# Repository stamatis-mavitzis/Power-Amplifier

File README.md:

<div align="center">

# Hi‑Fi Class‑AB Power Amplifier

### Stereo discrete power amplifier with dual 500 VA supplies, STM32 speaker protection, thermal monitoring, KiCad hardware, firmware, and measured prototype validation

**KiCad · Discrete Class‑AB · ≈±34.5 V Idle Rails · STM32G031K8 · Speaker Protection · Thermal Monitoring**

</div>

---

## Overview

This repository contains the design, implementation, firmware, fabrication files, and measured validation of a two-channel discrete **Hi‑Fi Class‑AB power amplifier** developed in **KiCad**.

The power-amplifier stage is based on the design principles of **Rod Elliott's Elliott Sound Products (ESP) Project 3A**. This implementation expands that reference design into a complete stereo amplifier system with:

- one dedicated **500 VA transformer per audio channel**;
- independent high-current rectification and filtering for the left and right channels;
- custom amplifier and power-supply PCBs;
- **MJL21193G / MJL21194G** complementary output devices;
- a dedicated **STM32G031K8 speaker-protection controller**;
- independent left/right DC monitoring;
- dual heatsink-temperature monitoring;
- relay-controlled speaker outputs;
- firmware for startup delay, fault handling, thermal protection, and status indication;
- measured electrical validation of the completed prototype.

The repository is intended to document the project from schematic design and PCB layout through assembly, firmware, bring-up, and bench testing.

---

## Project Status

The amplifier has progressed beyond the design-only stage.

Current status:

- amplifier PCBs assembled;
- power-supply hardware assembled;
- dual-transformer stereo supply implemented;
- STM32 protection system programmed and tested;
- left and right amplifier channels operational;
- speaker relays and protection functions tested;
- DC operating points measured;
- quiescent bias measured cold and warm;
- rail voltages measured at idle and under 8 Ω load;
- rail ripple measured under load;
- frequency-response checks completed;
- upper −3 dB point measured;
- final bench-test results recorded.

The project should therefore be described as a **built and functionally validated prototype**, not only as a planned or fabrication-ready design.

---

## Table of Contents

- [Key Features](#key-features)
- [Technical Summary](#technical-summary)
- [Measured Performance](#measured-performance)
- [System Architecture](#system-architecture)
- [Power Amplifier](#power-amplifier)
- [Power Supply](#power-supply)
- [STM32 Protection Controller](#stm32-protection-controller)
- [Protection Logic](#protection-logic)
- [Thermal Management](#thermal-management)
- [PCB Design Strategy](#pcb-design-strategy)
- [Grounding Strategy](#grounding-strategy)
- [Major Components](#major-components)
- [Test Equipment](#test-equipment)
- [Repository Structure](#repository-structure)
- [Manufacturing Files](#manufacturing-files)
- [Bring-Up and Validation](#bring-up-and-validation)
- [Measurement Limitations](#measurement-limitations)
- [Safety](#safety)
- [Design Tools](#design-tools)
- [Reference Design and Credits](#reference-design-and-credits)
- [Author](#author)

---

## Key Features

### Audio Power Stage

- Two-channel discrete **Class‑AB** architecture
- One amplifier PCB per channel
- Complementary bipolar output stage
- **MJL21193G / MJL21194G** complementary output transistor pair
- **BD139 / BD140** driver stage
- **0.33 Ω / 5 W** emitter resistors
- Through-hole power devices for serviceability and heatsink mounting
- Dedicated external heatsink for each amplifier channel
- On-board **3 A** positive- and negative-rail fuses

### Main Power Supply

- **2 × 500 VA transformers**
- One transformer dedicated to the **left channel**
- One transformer dedicated to the **right channel**
- Nominal dual low-voltage secondary windings
- Measured transformer secondary voltages of approximately **25.5–25.7 VRMS per half-secondary**
- High-current bridge rectification
- **KBPC3506WP** bridge rectifier in the power-supply design
- Four **4700 µF** reservoir capacitors on the power-supply schematic
- Measured idle rails of approximately **+34.5 V / −34.5 V**
- Measured loaded rails of approximately **±33.5 to ±33.7 V** with an 8 Ω load

### Protection and Monitoring

- **ST NUCLEO‑G031K8**
- **STM32G031K8** microcontroller
- Independent left/right amplifier-output monitoring
- Independent left/right heatsink-temperature monitoring
- 10 kΩ NTC thermistors
- Startup speaker delay
- Persistent-DC fault detection
- Overtemperature shutdown
- Sensor-fault handling
- Latched fault handling and reset
- Relay-controlled left/right speaker outputs
- Front-panel status indication

### Mechanical and Thermal Design

- Large external heatsinks
- Passive natural-convection cooling
- Power transistors positioned near PCB edges for heatsink mounting
- Electrical insulation between power-transistor tabs and heatsink where required
- Metal-chassis integration
- Star-ground implementation
- Chassis protective-earth bonding
- High-current speaker and supply wiring separated from low-level input wiring

---

## Technical Summary

| Parameter | Final implementation |
|---|---|
| Amplifier topology | Discrete Class‑AB |
| Number of channels | 2 |
| Main transformers | **2 × 500 VA**, one per channel |
| Measured secondary voltage | ≈25.5–25.7 VRMS from each outer secondary lead to center tap |
| Measured idle rails | ≈+34.5 V / −34.5 V |
| Measured rails under 8 Ω test load | ≈±33.5 to ±33.7 V |
| Output devices | **MJL21194G (NPN) / MJL21193G (PNP)** |
| Output-device package | **TO‑264, through-hole** |
| Driver devices | **BD139 / BD140** |
| Output emitter resistors | **R13 / R14 = 0.33 Ω, 5 W** |
| Amplifier rail fuses | **3 A** |
| Protection controller | ST NUCLEO‑G031K8 |
| MCU | STM32G031K8 |
| Speaker relays | 2 × Omron G2RL‑1A‑E‑DC12 |
| Relay driver | BC337 NPN |
| Temperature sensing | 2 × 10 kΩ NTC |
| Cooling | External heatsinks, passive natural convection |
| Audio inputs | RCA |
| Speaker outputs | Chassis-mounted binding terminals |
| PCB CAD | KiCad |

---

# Measured Performance

The following values were measured on the completed prototype. They are reported as **bench-test results**, not as guaranteed production specifications.

## Transformer Secondary Voltages

Measured from each AC secondary lead to the center tap:

| Measurement | Left | Right |
|---|---:|---:|
| AC1 → center tap | 25.652 VRMS | 25.628 VRMS |
| AC2 → center tap | 25.631 VRMS | 25.516 VRMS |

The measurements show good agreement between the two transformer channels.

## DC Supply Rails

### Idle

| Rail | Left | Right |
|---|---:|---:|
| Positive | +34.521 V | +34.566 V |
| Negative | −34.532 V | −34.522 V |

### Under 8 Ω Amplifier Load

| Rail | Left | Right |
|---|---:|---:|
| Positive | +33.534 V | +33.678 V |
| Negative | −33.560 V | −33.701 V |

The measured rail reduction under the recorded load condition is approximately 0.8–1.0 V compared with idle.

## Rail Ripple Under 8 Ω Load

Recorded ripple values:

| Rail | Left | Right |
|---|---:|---:|
| Positive rail | 1.5 V | 1.4 V |
| Negative rail | 1.6 V | 1.4 V |

These values are reproduced as recorded in the measurement log. They should not be interpreted as a different RMS or peak-to-peak quantity unless the oscilloscope measurement mode used during the test is also specified.

## Quiescent Bias

Bias was measured as the voltage across **R13 + R14**.

Because each emitter resistor is **0.33 Ω**, the combined resistance is **0.66 Ω**.

| Channel | Cold voltage | Approx. cold current | Warm voltage | Approx. warm current |
|---|---:|---:|---:|---:|
| Left | 41.700 mV | 63.2 mA | 52.55 mV | 79.6 mA |
| Right | 41.730 mV | 63.2 mA | 55.71 mV | 84.4 mA |

The increase from cold to warm operation is documented so that bias thermal behaviour remains traceable.

## DC Output Offset

Initial recorded DC-offset measurements:

| Channel | DC offset |
|---|---:|
| Left | −54.54 mV |
| Right | −28.203 mV |

A later no-signal measurement recorded:

| Channel | Amplifier output |
|---|---:|
| Left | +42.300 mV |
| Right | −23.764 mV |

Because these measurements were taken at different points in the test sequence, they are retained separately rather than combined into a single nominal value.

## Frequency Response and Voltage Gain

With:

- input signal: **1.2 V peak-to-peak**;
- sine-wave test;
- test frequencies: **20 Hz, 50 Hz, 100 Hz, 500 Hz, 1 kHz, 5 kHz, 10 kHz, 20 kHz**;

the recorded output was approximately:

- Left: **22.6 V peak-to-peak**
- Right: **22.6 V peak-to-peak**

This corresponds to:

- voltage gain: **18.83 V/V**
- voltage gain: **25.50 dB**

No significant amplitude reduction was recorded over the tested **20 Hz to 20 kHz** audio band.

The recorded **upper −3 dB frequency** is approximately:

**250 kHz**

The protection controller may interpret very-low-frequency content below approximately **15 Hz** as a DC-like condition. This is a **protection-system behaviour**, not the amplifier's measured low-frequency −3 dB cutoff.

## 8 Ω Loaded Signal Test

With an **8 Ω load** and **Vin = 1.2 V peak-to-peak**:

| Channel | Vout | Gain V/V | Gain dB | Approx. power into 8 Ω |
|---|---:|---:|---:|---:|
| Left | 27.2 Vpp | 22.67 | 27.11 dB | 11.56 W |
| Right | 26.6 Vpp | 22.17 | 26.91 dB | 11.06 W |

The right-channel gain is **26.91 dB** from the recorded 26.6 Vpp / 1.2 Vpp values.

This test point is **not** the maximum unclipped output-power rating of the amplifier. It only documents the specific load and signal level used during that measurement.

## Protection-System Measurements

Healthy amplifier outputs produced the following DC-sense ADC voltages:

| Channel | ADC sense voltage |
|---|---:|
| Left | 1.6014 V |
| Right | 1.5969 V |

Relay-driver base voltage with relays ON:

| Channel | Base voltage |
|---|---:|
| Left | 3.2932 V |
| Right | 3.2931 V |

Relay-coil voltage with relays ON:

| Channel | Coil voltage |
|---|---:|
| Left | 11.723 V |
| Right | 11.735 V |

NTC room-temperature readings:

| Sensor | Voltage |
|---|---:|
| NTC 1 | 1.1230 V |
| NTC 2 | 1.1225 V |

The remaining protection-system functional tests were recorded as **passed**.

---

## System Architecture

The complete amplifier is divided into three main functional paths:

1. **Audio path**
2. **Power path**
3. **Protection path**

### Audio Path

```text
RCA INPUT
    │
    ▼
┌───────────────────────┐
│  Discrete Class‑AB    │
│  Power Amplifier      │
│                       │
│  • Input stage        │
│  • Voltage gain stage │
│  • Bias network       │
│  • Driver stage       │
│  • Output stage       │
└───────────┬───────────┘
            │
            ▼
┌───────────────────────┐
│  Speaker Protection   │
│  Relay                │
└───────────┬───────────┘
            │
            ▼
       SPEAKER OUT
```

### Power Path

```text
                         230 VAC MAINS
                               │
               ┌───────────────┴───────────────┐
               ▼                               ▼
      500 VA TRANSFORMER #1           500 VA TRANSFORMER #2
           LEFT CHANNEL                    RIGHT CHANNEL
               │                               │
               ▼                               ▼
       RECTIFIER + FILTER              RECTIFIER + FILTER
               │                               │
               ▼                               ▼
        LEFT ±34 V RAILS                RIGHT ±34 V RAILS
               │                               │
               ▼                               ▼
        LEFT AMPLIFIER                  RIGHT AMPLIFIER
```

Each channel therefore has its own transformer and power-supply path, reducing shared supply impedance between the two amplifier channels.

### Protection Path

```text
Left Amp Output  ─────► DC Sense ───────┐
Right Amp Output ─────► DC Sense ───────┤
Left Heatsink NTC ────► Temp Sense ─────┤
Right Heatsink NTC ───► Temp Sense ─────┤
                                         ▼
                              ┌────────────────────┐
                              │   STM32G031K8      │
                              │                    │
                              │ • ADC acquisition  │
                              │ • Startup delay    │
                              │ • Fault logic      │
                              │ • Thermal logic    │
                              └─────────┬──────────┘
                                        │
                                  Relay drivers
                                        │
                                  ┌─────┴─────┐
                                  ▼           ▼
                              Left relay  Right relay
                                  │           │
                                  ▼           ▼
                              Left spk.   Right spk.
```

---

## Power Amplifier

The audio section uses a conventional **discrete Class‑AB power-amplifier topology** based on the principles of ESP Project 3A.

Functional stages include:

1. **Input stage** — accepts the low-level audio signal.
2. **Voltage-amplification stage** — provides the main voltage gain.
3. **Bias network** — establishes Class‑AB idle current.
4. **Driver stage** — provides base drive for the power output devices.
5. **Complementary output stage** — supplies current to the loudspeaker.

### Output Devices

| Reference | Device | Polarity | Package |
|---|---|---|---|
| Q7 | **MJL21193G** | PNP | TO‑264 |
| Q8 | **MJL21194G** | NPN | TO‑264 |

The output devices are mounted close to the PCB edge so that they can be attached directly to the external heatsink.

Electrical isolation hardware and thermal-interface material must be used where required by the mechanical installation.

### Driver Stage

The amplifier uses complementary **BD139 / BD140** driver transistors.

### Output Emitter Resistors

- **R13 = 0.33 Ω / 5 W**
- **R14 = 0.33 Ω / 5 W**

These resistors are also used as convenient measurement points for the output-stage quiescent current.

### Rail Protection

Each amplifier board includes:

- **3 A fuse in the positive rail**
- **3 A fuse in the negative rail**

These fuses protect the amplifier board but do not replace the required mains-side transformer protection.

---

## Power Supply

The final stereo implementation uses a **dual-mono-style power architecture**:

- one **500 VA transformer** for the left channel;
- one **500 VA transformer** for the right channel.

Each transformer has a center-tapped secondary arrangement and feeds its own rectifier/filter path.

Measured secondary voltages are approximately **25.5–25.7 VRMS from each outer secondary lead to the center tap**.

After rectification and reservoir filtering, the measured idle rails are approximately:

```text
+34.5 V
  0 V
−34.5 V
```

Under the recorded 8 Ω load test, the rails remained approximately **±33.5 to ±33.7 V**.

### Rectification and Filtering

The power-supply schematic uses:

- **Diotec KBPC3506WP** bridge rectifier;
- four **4700 µF** reservoir capacitors;
- local bypass capacitors;
- heavy-current connections for the DC rails and common return.

### Power-Supply Design Priorities

- short transformer-to-rectifier wiring;
- short rectifier-to-reservoir-capacitor paths;
- adequate conductor cross-section;
- deliberate star grounding;
- high-current speaker returns separated from input ground;
- secure protective-earth bonding;
- mains-rated switchgear, wiring, insulation, and fuse protection;
- independent left/right channel supply paths.

---

## STM32 Protection Controller

Speaker protection is implemented with an **ST NUCLEO‑G031K8** carrying the **STM32G031K8** microcontroller.

The controller supervises both amplifier channels and only connects the loudspeakers when the monitored conditions are safe.

### ADC Inputs

The controller monitors:

| Signal | MCU pin / ADC input |
|---|---|
| TEMP1 | PA0 / A0 |
| TEMP2 | PA1 / A1 |
| DC_LEFT | PA4 / A2 |
| DC_RIGHT | PA5 / A3 |

The firmware uses ADC averaging to improve measurement stability.

### Protection Timing and Thermal Thresholds

Current firmware configuration includes:

- startup delay: **3 s**
- periodic protection sampling
- overtemperature trip: approximately **100 °C**
- thermal reset threshold: approximately **90 °C**
- latched fault handling where applicable
- manual fault-reset support

### Controlled Outputs

The controller operates:

- left speaker relay;
- right speaker relay;
- status and fault LEDs;
- relay drivers through BC337 transistors.

---

## Protection Logic

### Startup Delay

At power-up, the loudspeakers remain disconnected while the MCU initializes and checks the monitored conditions.

```text
POWER ON
   │
   ▼
MCU INITIALIZATION
   │
   ▼
ADC + GPIO INITIALIZATION
   │
   ▼
VERIFY SENSOR / DC CONDITIONS
   │
   ▼
3 s STARTUP DELAY
   │
   ▼
ENABLE SPEAKER RELAYS
```

If a fault exists, the speaker relays remain disabled.

### DC Protection

The left and right amplifier outputs are independently monitored through conditioned ADC inputs.

A persistent abnormal positive or negative DC component causes the controller to disable the associated speaker connection.

```text
ABNORMAL DC
     │
     ▼
STM32 FAULT DECISION
     │
     ▼
RELAY DRIVER OFF
     │
     ▼
SPEAKER DISCONNECTED
```

The healthy operating point of the DC-sense channels is approximately **1.6 V**, allowing the circuit to detect excursions in either direction.

### Very-Low-Frequency Behaviour

The implemented protection logic may classify signals below approximately **15 Hz** as DC-like.

This should not be confused with the amplifier's audio-band frequency response.

### Temperature Protection

Each channel uses a **10 kΩ NTC thermistor** attached to the thermal system.

```text
LEFT HEATSINK  ──► NTC ──► ADC
RIGHT HEATSINK ──► NTC ──► ADC
```

The controller can disconnect the loudspeakers when the thermal trip threshold is reached.

### Relay Drive

The STM32 does not energize the relay coils directly.

Each channel uses:

```text
STM32 GPIO
    │
    ▼
Base resistor
    │
    ▼
BC337 NPN
    │
    ▼
12 V relay coil
    │
    └── Flyback diode
```

Measured relay-coil voltage in the ON state is approximately **11.7 V**.

### Speaker Relays

Two **Omron G2RL‑1A‑E‑DC12** relays are used:

- one for the left channel;
- one for the right channel.

---

## Thermal Management

The amplifier is designed for passive cooling using external chassis heatsinks.

The thermal design includes:

- one external heatsink per amplifier channel;
- direct mounting of the TO‑264 power transistors;
- electrical insulation where required;
- thermal compound / thermal interface material;
- NTC sensing;
- firmware-based overtemperature protection;
- natural-convection airflow;
- no fan dependency.

The output-stage bias was measured both cold and after thermal stabilization to document thermal drift.

---

## PCB Design Strategy

The PCB layout was developed with audio performance, current handling, serviceability, and manufacturability in mind.

### High-Current Paths

High-current paths include:

- rectifier connections;
- reservoir-capacitor charging loops;
- ± rail distribution;
- output-stage supply paths;
- speaker-output routing;
- speaker-return current;
- relay contacts.

These paths should be kept short and wide.

### Small-Signal Paths

Sensitive nodes include:

- RCA input;
- input-stage circuitry;
- feedback network;
- bias-related nodes;
- low-level signal ground.

These are kept away from rectifier, relay-coil, transformer, and speaker-current paths as much as practical.

### Serviceability

Through-hole components are used extensively so that stressed devices, connectors, relays, drivers, and power transistors can be replaced during repair or development.

---

## Grounding Strategy

The final system uses a deliberate **star-ground approach**.

Both transformer center taps are brought to the central high-current ground reference, together with the appropriate power-supply returns.

The grounding strategy distinguishes between:

```text
SENSITIVE SIGNAL GROUND
         │
         ▼
CENTRAL / STAR REFERENCE
         ▲
         │
HIGH-CURRENT POWER GROUND
```

Design goals:

- prevent rectifier charging current from flowing through input-signal ground;
- keep feedback references electrically quiet;
- keep speaker return as a high-current path;
- avoid long shared ground traces;
- minimize hum and channel interaction;
- keep protection-controller current from disturbing the analog signal reference.

The metal chassis protective earth is treated separately from the audio star-ground function and must remain securely bonded for safety.

---

## Major Components

| Function | Selected component / specification |
|---|---|
| NPN output transistor | **MJL21194G** |
| PNP output transistor | **MJL21193G** |
| Driver transistors | **BD139 / BD140** |
| Output emitter resistors | **0.33 Ω / 5 W** |
| Amplifier rail fuses | **3 A** |
| Main transformers | **2 × 500 VA**, one per channel |
| Main bridge rectifier | **Diotec KBPC3506WP** |
| Reservoir capacitors | **4 × 4700 µF** on the power-supply schematic |
| Protection development board | **ST NUCLEO‑G031K8** |
| MCU | **STM32G031K8** |
| Speaker relays | **Omron G2RL‑1A‑E‑DC12** |
| Relay driver | **BC337** |
| Temperature sensors | **10 kΩ NTC** |
| Audio input | RCA |
| Speaker output | Chassis-mounted binding terminals |
| Cooling | External passive heatsinks |

---

## Test Equipment

The completed amplifier was tested using the following bench instruments:

| Instrument | Model | Use |
|---|---|---|
| Oscilloscope | **UNI‑T UPO1202** | Waveform, amplitude, ripple, frequency-response and output measurements |
| Function / signal generator | **OWON DGE1030** | Sine-wave test-signal generation |
| Digital multimeter | **OWON XDM2041** | DC rails, bias, offsets, relay voltages, sensor voltages and continuity checks |

Measurement results in this README should be interpreted together with the stated load, signal amplitude, and test condition.

---

## Repository Structure

```text
Power-Amplifier/
│
├── Firmware/
│   └── STM32/
│
├── Images/
│
├── KiCad/
│
├── Libraries/
│
├── Manufacturing/
│
├── PDF/
│
├── Schematics/
│
└── README.md
```

### Directory Overview

| Path | Contents |
|---|---|
| `Firmware/STM32/` | STM32 source, configuration, project files, and protection-controller firmware |
| `Images/` | Project photographs, PCB renders, diagrams, and screenshots |
| `KiCad/` | Editable KiCad schematic and PCB project files |
| `Libraries/` | Project-specific KiCad symbols and footprints |
| `Manufacturing/` | Gerber and drill outputs for PCB fabrication |
| `PDF/` | PDF exports and project documentation |
| `Schematics/` | Exported schematic drawings |
| `README.md` | Main project overview and measured validation summary |

---

## Manufacturing Files

The fabrication package contains the files required by a typical PCB manufacturer.

### Gerber Outputs

Typical exported layers include:

- copper;
- solder mask;
- silkscreen;
- board outline / `Edge.Cuts`;
- other fabrication layers required by the board.

### Drill Outputs

The project distinguishes between:

- **PTH** — plated through holes;
- **NPTH** — non-plated mechanical holes, where present.

Gerber files and drill files are both required for a complete PCB manufacturing package.

---

## Bring-Up and Validation

The completed hardware was commissioned using a staged validation procedure.

### 1. Visual and Assembly Inspection

- verify transistor orientation and pinout;
- verify MJL21193G / MJL21194G mounting;
- verify insulation from heatsink where required;
- verify electrolytic polarity;
- verify diode and relay orientation;
- inspect solder joints and high-current connections.

### 2. Unpowered Electrical Checks

- continuity;
- rail-to-ground short checks;
- transistor junction checks;
- ground-path verification;
- output-stage connection verification.

### 3. Power-Supply Validation

- verify transformer secondaries;
- verify bridge-rectifier polarity;
- measure positive and negative rails;
- compare left and right channels;
- measure rail behaviour under load.

### 4. Controlled Amplifier Power-Up

- loudspeakers disconnected initially;
- monitor DC offset;
- monitor bias voltage;
- monitor transistor temperature;
- verify no uncontrolled rail current.

### 5. Protection Validation

- startup delay;
- DC monitoring;
- relay operation;
- NTC sensing;
- thermal handling;
- sensor-fault behaviour;
- fault indication;
- reset behaviour.

### 6. Signal Validation

- apply a known sine-wave input;
- observe the amplifier output on the oscilloscope;
- test with a suitable resistive load;
- verify operation across the audio-frequency range;
- progressively increase signal level while monitoring rails and temperature.

---

## Measurement Limitations

The current measurement set documents successful functional operation and several important electrical characteristics.

The following values have **not** been established as formal amplifier specifications and should not be claimed without additional controlled measurements:

- THD / THD+N;
- signal-to-noise ratio;
- channel separation / crosstalk;
- maximum continuous output power;
- maximum unclipped output voltage at clipping;
- full thermal-rise curve versus continuous output power;
- damping factor;
- slew rate.

Because no additional measurements are currently available, this README reports only the values that were actually recorded or that can be directly calculated from those recorded values.

---

## Safety

> This project interfaces with **230 VAC mains voltage** and contains high-current circuitry and large energy-storage capacitors. Incorrect construction or testing can cause electric shock, fire, equipment damage, or component failure.

Important safety requirements include:

- correctly rated mains fuse protection;
- protective-earth bonding to the metal chassis;
- mains-rated switch and wiring;
- suitable insulation;
- correct conductor cross-section;
- strain relief;
- secure transformer mounting;
- adequate creepage and clearance;
- insulated exposed mains connections;
- safe transistor/heatsink insulation;
- awareness that reservoir capacitors retain stored energy after shutdown.

**Never service, modify, or probe the mains section while the unit is energized.**

---

## Design Tools

| Tool / source | Purpose |
|---|---|
| **KiCad** | Schematic capture, PCB design, footprints, and fabrication outputs |
| **STM32CubeMX** | STM32 peripheral and project configuration |
| **STM32CubeIDE** | STM32 firmware development, programming, and debugging |
| **Mouser Electronics** | Component sourcing |
| **Manufacturer datasheets** | Electrical, thermal, package, and footprint verification |
| **Git / GitHub** | Version control and repository documentation |

---

## Reference Design and Credits

The core amplifier topology is based on:

**Rod Elliott — Elliott Sound Products (ESP), Project 3A Power Amplifier**

Reference:

https://sound-au.com/project3a.htm

Credit for the original amplifier topology belongs to **Rod Elliott / Elliott Sound Products**.

This repository documents the project-specific implementation around that topology, including:

- PCB implementation;
- component selection;
- dual 500 VA transformer architecture;
- power-supply integration;
- STM32 protection controller;
- DC monitoring;
- temperature monitoring;
- relay control;
- firmware;
- grounding;
- chassis integration;
- fabrication files;
- prototype assembly;
- measured validation.

---

## Engineering Goals

The project was developed around the following objectives:

- reliable discrete Class‑AB amplification;
- independent left/right power delivery;
- speaker protection against persistent DC;
- temperature monitoring and shutdown;
- low-noise PCB layout;
- deliberate grounding;
- practical current handling;
- serviceable construction;
- sourceable components;
- reproducible PCB fabrication;
- embedded protection firmware;
- measured bench validation;
- clear engineering documentation.

---

## Author

**Stamatis Mavitzis**  
Electrical & Computer Engineering

Designed in **KiCad**.

---

<div align="center">

### Hi‑Fi Power Amplifier · Engineering Project

*Discrete Class‑AB audio amplification, dual 500 VA power supplies, STM32 protection, PCB design, firmware, manufacturing files, and measured prototype validation.*

</div>

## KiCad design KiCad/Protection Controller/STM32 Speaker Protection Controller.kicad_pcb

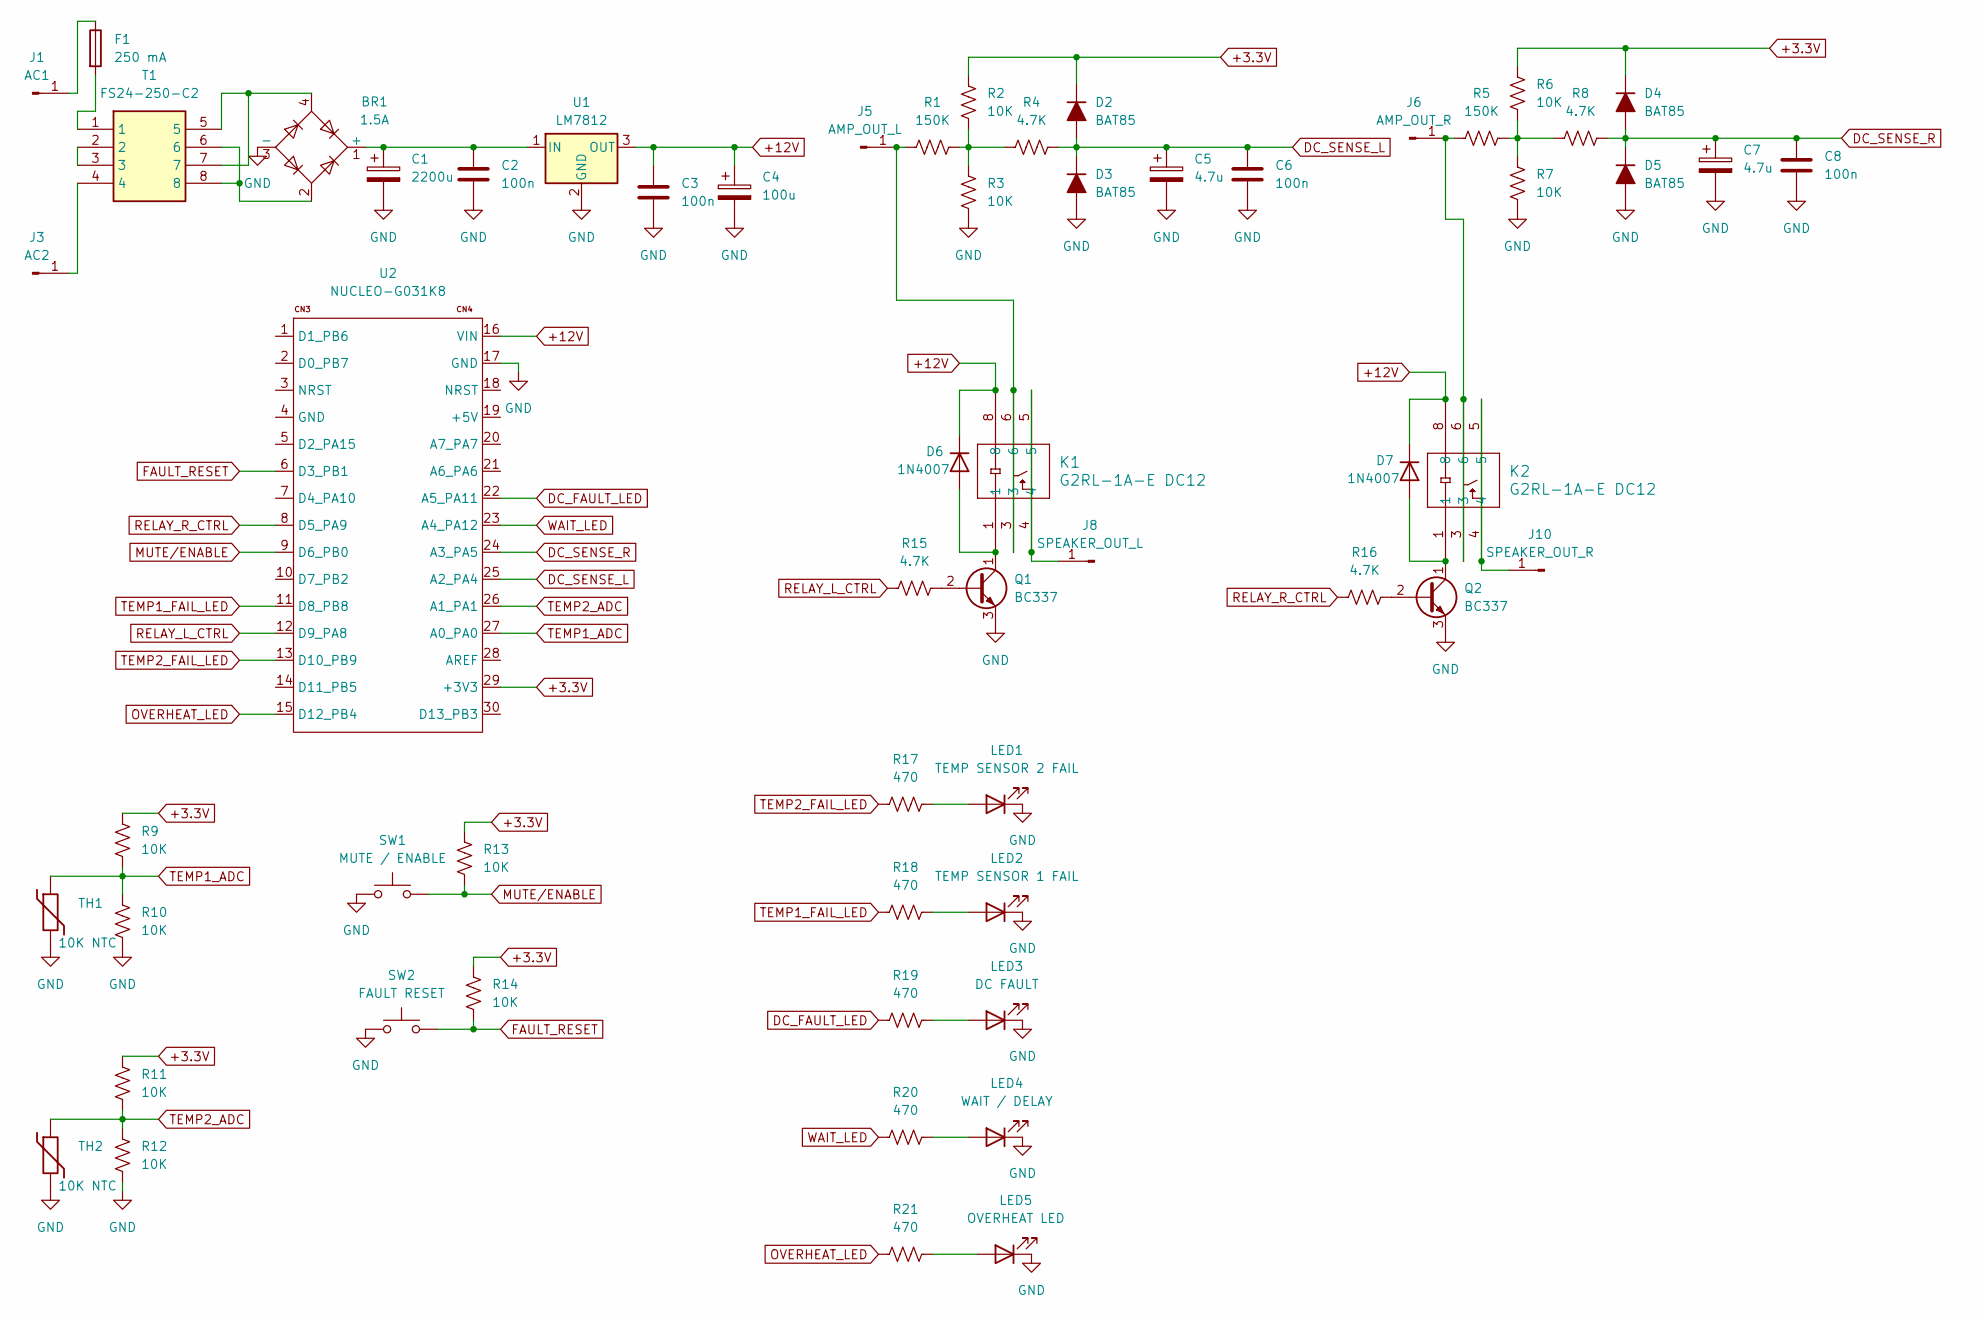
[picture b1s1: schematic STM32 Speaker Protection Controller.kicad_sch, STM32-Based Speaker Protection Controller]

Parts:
BR1: 1.5A; Diode_Bridge_Round_D9.8mm
C1: 2200u; CP_Radial_D12.5mm_P5.00mm
C2, C3, C6, C8: 100n; C_Disc_D5.0mm_W2.5mm_P2.50mm
C4: 100u; CP_Radial_D6.3mm_P2.50mm
C5, C7: 4.7u; CP_Radial_D6.3mm_P2.50mm
D2, D3, D4, D5: BAT85; D_DO-35_SOD27_P7.62mm_Horizontal
D6, D7: 1N4007; D_DO-41_SOD81_P10.16mm_Horizontal
F1: 250 mA; Fuseholder_Cylinder-5x20mm_Stelvio-Kontek_PTF78_Horizontal_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
J1: AC1; SolderWire-6sqmm_1x01_D3.5mm_OD7mm
J3: AC2; SolderWire-6sqmm_1x01_D3.5mm_OD7mm
J5: AMP_OUT_L; SolderWire-6sqmm_1x01_D3.5mm_OD7mm
J6: AMP_OUT_R; SolderWire-6sqmm_1x01_D3.5mm_OD7mm
J8: SPEAKER_OUT_L; SolderWire-6sqmm_1x01_D3.5mm_OD7mm
J10: SPEAKER_OUT_R; SolderWire-6sqmm_1x01_D3.5mm_OD7mm
K1, K2: G2RL-1A-E DC12; Relay_SPST_Omron_G2RL-1A-E
LED1: TEMP SENSOR 2 FAIL; LED_D5.0mm
LED2: TEMP SENSOR 1 FAIL; LED_D5.0mm
LED3: DC FAULT; LED_D5.0mm
LED4: WAIT / DELAY; LED_D5.0mm
LED5: OVERHEAT LED; LED_D5.0mm
Q1, Q2: BC337; TO-92_Inline
R1, R5: 150K; R_Axial_DIN0204_L3.6mm_D1.6mm_P7.62mm_Horizontal
R2, R3, R6, R7, R9, R10, R11, R12, R13, R14: 10K; R_Axial_DIN0204_L3.6mm_D1.6mm_P7.62mm_Horizontal
R4, R8, R15, R16: 4.7K; R_Axial_DIN0204_L3.6mm_D1.6mm_P7.62mm_Horizontal
R17, R18, R19, R20, R21: 470; R_Axial_DIN0204_L3.6mm_D1.6mm_P7.62mm_Horizontal
SW1: MUTE / ENABLE; SW_PUSH_6mm_H5mm
SW2: FAULT RESET; SW_PUSH_6mm_H5mm
T1: FS24-250-C2; FS24250C2; Manufacturer_Part_Number FS24-250-C2; Mouser Part Number 553-FS24-250-C2
TH1, TH2: 10K NTC; TerminalBlock_Phoenix_MKDS-1,5-2_1x02_P5.00mm_Horizontal
U1: LM7812; TO-220-3_Vertical
U2: NUCLEO-G031K8

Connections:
+3.3V: D2.1 (K), D4.1 (K), R2.1, R6.1, R9.1, R11.1, R13.2, R14.2, U2.29 (+3V3)
+12V: C3.1, C4.1, D6.1 (K), D7.1 (K), K1.8, K2.8, U1.3 (OUT), U2.16 (VIN)
DC_FAULT_LED: R19.1, U2.22 (A5_PA11)
DC_SENSE_L: C5.1, C6.1, D2.2 (A), D3.1 (K), R4.2, U2.25 (A2_PA4)
DC_SENSE_R: C7.1, C8.1, D4.2 (A), D5.1 (K), R8.2, U2.24 (A3_PA5)
FAULT_RESET: R14.1, SW2.2, U2.6 (D3_PB1)
GND: BR1.3 (-), C1.2, C2.2, C3.2, C4.2, C5.2, C6.2, C7.2, C8.2, D3.2 (A), D5.2 (A), LED1.1 (K), LED2.1 (K), LED3.1 (K), LED4.1 (K), LED5.1 (K), Q1.3 (E), Q2.3 (E), R3.2, R7.2, R10.2, R12.2, SW1.1, SW2.1, TH1.2, TH2.2, U1.2 (GND), U2.17 (GND)
MUTE/ENABLE: R13.1, SW1.2, U2.9 (D6_PB0)
unnamed: BR1.1 (+), C1.1, C2.1, U1.1 (IN)
unnamed: BR1.2, T1.6, T1.8
unnamed: BR1.4, T1.5, T1.7
unnamed: D6.2 (A), K1.1, Q1.1 (C)
unnamed: D7.2 (A), K2.1, Q2.1 (C)
unnamed: F1.2, T1.1
unnamed: F1.1, J1.1 (Pin_1_1)
unnamed: J3.1 (Pin_1_1), T1.4
unnamed: J5.1 (Pin_1_1), K1.3, K1.6, R1.1
unnamed: J6.1 (Pin_1_1), K2.3, K2.6, R5.1
unnamed: J8.1 (Pin_1_1), K1.4, K1.5
unnamed: J10.1 (Pin_1_1), K2.4, K2.5
unnamed: LED1.2 (A), R17.2
unnamed: LED2.2 (A), R18.2
unnamed: LED3.2 (A), R19.2
unnamed: LED4.2 (A), R20.2
unnamed: LED5.2 (A), R21.2
unnamed: Q1.2 (B), R15.2
unnamed: Q2.2 (B), R16.2
unnamed: R1.2, R2.2, R3.1, R4.1
unnamed: R5.2, R6.2, R7.1, R8.1
unnamed: T1.2, T1.3
OVERHEAT_LED: R21.1, U2.15 (D12_PB4)
RELAY_L_CTRL: R15.1, U2.12 (D9_PA8)
RELAY_R_CTRL: R16.1, U2.8 (D5_PA9)
TEMP1_ADC: R9.2, R10.1, TH1.1, U2.27 (A0_PA0)
TEMP1_FAIL_LED: R18.1, U2.11 (D8_PB8)
TEMP2_ADC: R11.2, R12.1, TH2.1, U2.26 (A1_PA1)
TEMP2_FAIL_LED: R17.1, U2.13 (D10_PB9)
WAIT_LED: R20.1, U2.23 (A4_PA12)

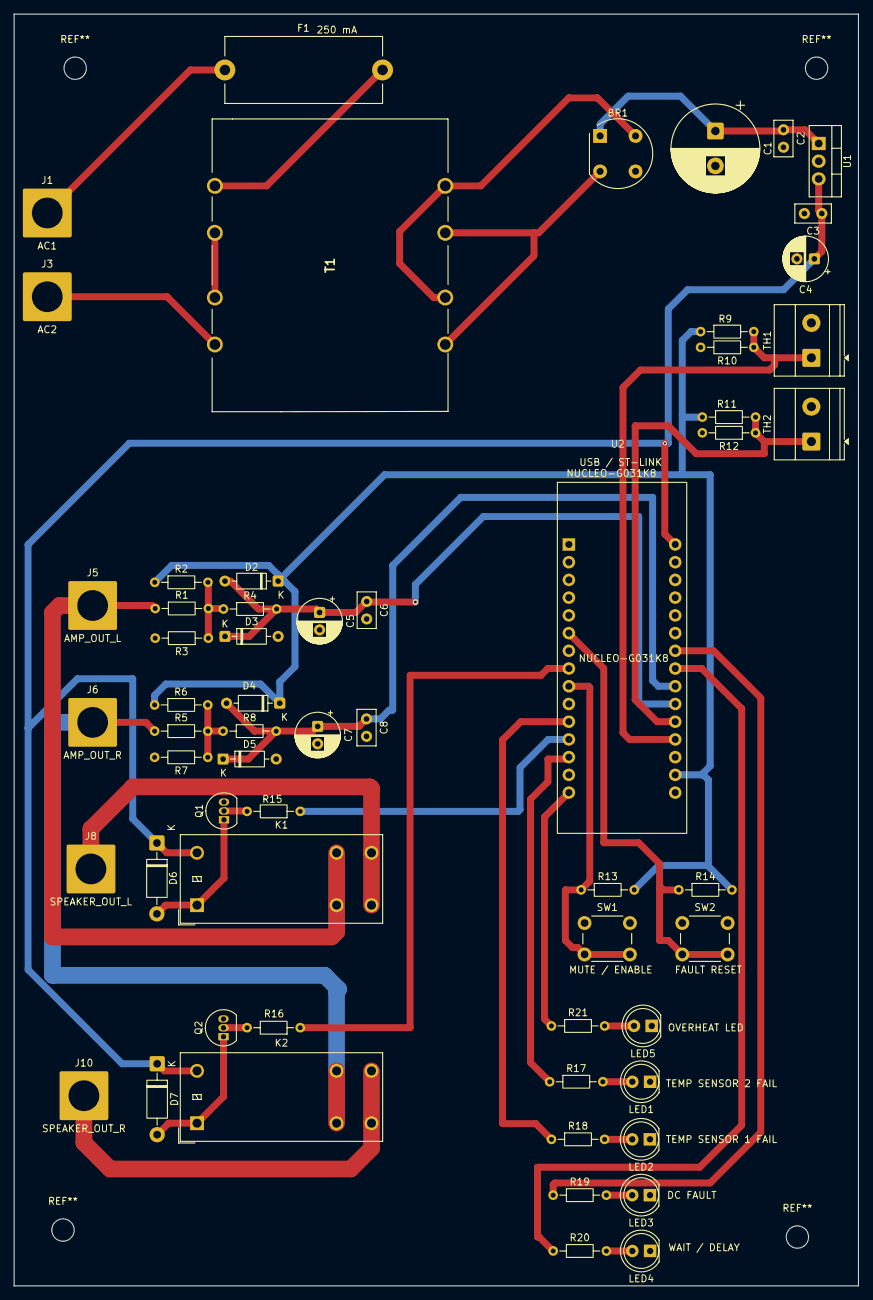
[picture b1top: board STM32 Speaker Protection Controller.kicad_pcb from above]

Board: 2 copper layers, 121.0 x 182.2 mm, 59 parts (0 on the bottom side), 38 nets.

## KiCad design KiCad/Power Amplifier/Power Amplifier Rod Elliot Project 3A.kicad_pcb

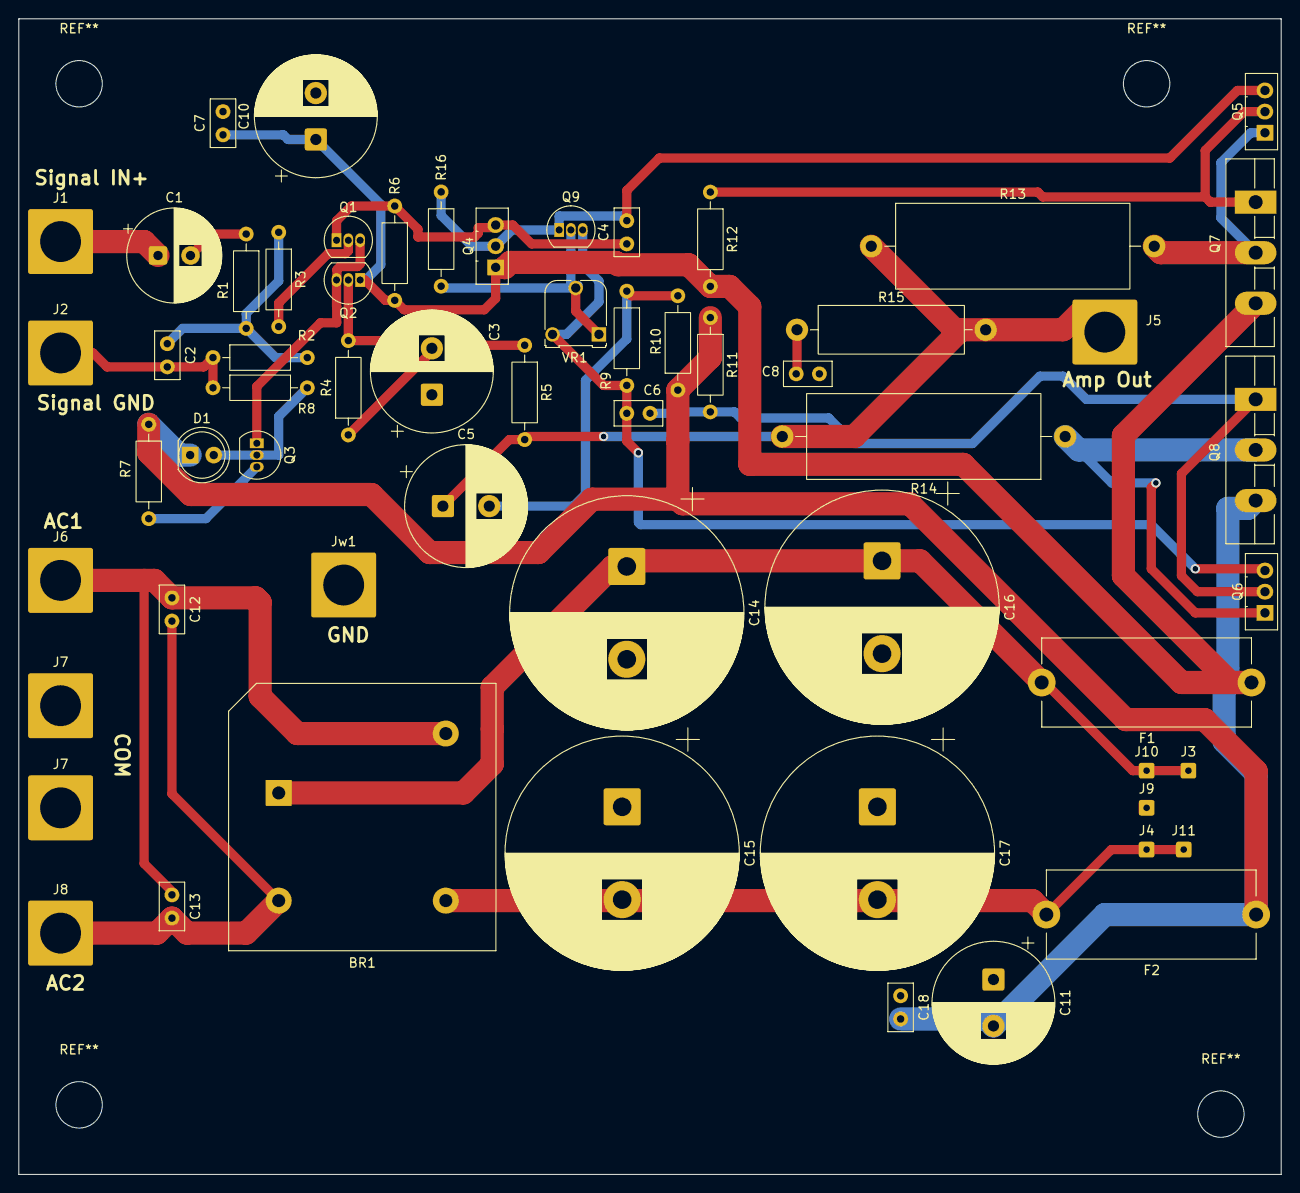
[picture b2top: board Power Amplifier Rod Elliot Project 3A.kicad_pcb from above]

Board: 2 copper layers, 136.0 x 124.5 mm, 60 parts (0 on the bottom side), 28 nets.

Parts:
BR1: Diotec KBPC3506WP; Diode_Bridge_28.6x28.6x7.3mm_P18.0mm_P11.6mm
C1: 4.7u; CP_Radial_D10.0mm_P3.50mm
C2, C4, C6: 100p; C_Disc_D5.0mm_W2.5mm_P2.50mm
C3, C5, C10, C11: 100u; CP_Radial_D13.0mm_P5.00mm
C7, C8, C12, C13, C18: 100n; C_Disc_D5.0mm_W2.5mm_P2.50mm
C14, C15, C16, C17: 4700u; CP_Radial_D25.0mm_P10.00mm_SnapIn
D1: LED; LED_D5.0mm
F1, F2: 3A; Fuseholder_Cylinder-5x20mm_Stelvio-Kontek_PTF78_Horizontal_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
J1: AUDIO IN; SolderWire-6sqmm_1x01_D3.5mm_OD7mm
J2: GND; SolderWire-6sqmm_1x01_D3.5mm_OD7mm
J3, J10: +35V; SolderWire-0.127sqmm_1x01_D0.48mm_OD1mm
J4, J11: -35V; SolderWire-0.127sqmm_1x01_D0.48mm_OD1mm
J5: SPEAKER OUT; SolderWire-6sqmm_1x01_D3.5mm_OD7mm
J6: V+; SolderWire-6sqmm_1x01_D3.5mm_OD7mm
J7, J7#2: COM; SolderWire-6sqmm_1x01_D3.5mm_OD7mm
J8: V-; SolderWire-6sqmm_1x01_D3.5mm_OD7mm
J9: GND; SolderWire-0.127sqmm_1x01_D0.48mm_OD1mm
Jw1: GND; SolderWire-6sqmm_1x01_D3.5mm_OD7mm
Q1, Q2, Q3, Q9: BC546; TO-92_Inline
Q4, Q6: BD140 MJE15035; TO-126-3_Vertical
Q5: BD139 MJE15034; TO-126-3_Vertical
Q7: MJL21193G; TO-264-3_Vertical
Q8: MJL21194G; TO-264-3_Vertical
R1, R3, R4, R16: 1K; R_Axial_DIN0207_L6.3mm_D2.5mm_P10.16mm_Horizontal
R2, R5, R8: 22K; R_Axial_DIN0207_L6.3mm_D2.5mm_P10.16mm_Horizontal
R6, R7: 560; R_Axial_DIN0207_L6.3mm_D2.5mm_P10.16mm_Horizontal
R9, R10, R11: 3K3; R_Axial_DIN0207_L6.3mm_D2.5mm_P10.16mm_Horizontal
R12: 220; R_Axial_DIN0207_L6.3mm_D2.5mm_P10.16mm_Horizontal
R13, R14: 0R33; R_Axial_Power_L25.0mm_W9.0mm_P30.48mm
R15: 10; R_Axial_DIN0516_L15.5mm_D5.0mm_P20.32mm_Horizontal
VR1: 2K; Potentiometer_Runtron_RM-065_Vertical

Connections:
+35V: BR1.1 (+), C14.1, C16.1, F1.2, J3.1 (Pin_1_1), J10.1 (Pin_1_1)
-35V: BR1.3 (-), C15.2, C17.2, F2.2, J4.1 (Pin_1_1), J11.1 (Pin_1_1)
GND: C3.1, C7.2, C8.2, C10.2, C11.1, C14.2, C15.1, C16.2, C17.1, C18.1, J7.1 (Pin_1_1), J7#2.1 (Pin_1_1), J9.1 (Pin_1_1), Jw1.1 (Pin_1_1)
unnamed: C1.2, R1.1
unnamed: C2.1, R1.2, R2.2, R3.1
unnamed: C3.2, R4.1
unnamed: C5.2, R9.1, R10.2
unnamed: C8.1, R15.1
unnamed: D1.2 (A), Q3.2 (B), R8.2
unnamed: C11.2, C18.2, D1.1 (K), F2.1, Q8.3 (E), R7.1, R10.1, R11.1
unnamed: C1.1, J1.1 (Pin_1_1)
unnamed: C5.1, J5.1 (Pin_1_1), R5.2, R13.1, R14.2, R15.2
unnamed: BR1.4, C12.1, C13.1, J6.1 (Pin_1_1)
unnamed: BR1.2, C12.2, C13.2, J8.1 (Pin_1_1)
unnamed: Q1.2 (B), R3.2
unnamed: C4.1, Q1.1 (C), Q4.3 (B), R6.1
unnamed: Q1.3 (E), Q2.3 (E), Q3.1 (C)
unnamed: Q2.2 (B), R4.2, R5.1
unnamed: C7.1, C10.1, F1.1, Q2.1 (C), Q4.1 (E), Q7.3 (E), R6.2, R12.2
unnamed: Q3.3 (E), R7.2
unnamed: C4.2, Q4.2 (C), Q5.3 (B), Q9.1 (C), R16.2
unnamed: Q5.2 (C), Q7.1 (B), R12.1
unnamed: Q5.1 (E), Q7.2 (C), R13.2
unnamed: C6.1, Q6.3 (B), Q9.3 (E), R9.2, VR1.3
unnamed: C6.2, Q6.2 (C), Q8.1 (B), R11.2
unnamed: Q6.1 (E), Q8.2 (C), R14.1
unnamed: Q9.2 (B), R16.1, VR1.1, VR1.2
SIGNAL_GND: C2.2, J2.1 (Pin_1_1), R2.1, R8.1

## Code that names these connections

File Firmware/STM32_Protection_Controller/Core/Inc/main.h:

/* USER CODE BEGIN Header */
/**
  ******************************************************************************
  * @file           : main.h
  * @brief          : Header for main.c file.
  *                   This file contains the common defines of the application.
  ******************************************************************************
  * @attention
  *
  * Copyright (c) 2026 STMicroelectronics.
  * All rights reserved.
  *
  * This software is licensed under terms that can be found in the LICENSE file
  * in the root directory of this software component.
  * If no LICENSE file comes with this software, it is provided AS-IS.
  *
  ******************************************************************************
  */
/* USER CODE END Header */

/* Define to prevent recursive inclusion -------------------------------------*/
#ifndef __MAIN_H
#define __MAIN_H

#ifdef __cplusplus
extern "C" {
#endif

/* Includes ------------------------------------------------------------------*/
#include "stm32g0xx_hal.h"

/* Private includes ----------------------------------------------------------*/
/* USER CODE BEGIN Includes */

/* USER CODE END Includes */

/* Exported types ------------------------------------------------------------*/
/* USER CODE BEGIN ET */

/* USER CODE END ET */

/* Exported constants --------------------------------------------------------*/
/* USER CODE BEGIN EC */

/* USER CODE END EC */

/* Exported macro ------------------------------------------------------------*/
/* USER CODE BEGIN EM */

/* USER CODE END EM */

/* Exported functions prototypes ---------------------------------------------*/
void Error_Handler(void);

/* USER CODE BEGIN EFP */

/* USER CODE END EFP */

/* Private defines -----------------------------------------------------------*/
#define TEMP2_FAIL_LED_Pin GPIO_PIN_9
#define TEMP2_FAIL_LED_GPIO_Port GPIOB
#define TEMP1_ADC_Pin GPIO_PIN_0
#define TEMP1_ADC_GPIO_Port GPIOA
#define TEMP2_ADC_Pin GPIO_PIN_1
#define TEMP2_ADC_GPIO_Port GPIOA
#define DC_SENSE_L_Pin GPIO_PIN_4
#define DC_SENSE_L_GPIO_Port GPIOA
#define DC_SENSE_R_Pin GPIO_PIN_5
#define DC_SENSE_R_GPIO_Port GPIOA
#define MUTE_ENABLE_Pin GPIO_PIN_0
#define MUTE_ENABLE_GPIO_Port GPIOB
#define FAULT_RESET_Pin GPIO_PIN_1
#define FAULT_RESET_GPIO_Port GPIOB
#define RELAY_L_CTRL_Pin GPIO_PIN_8
#define RELAY_L_CTRL_GPIO_Port GPIOA
#define RELAY_R_CTRL_Pin GPIO_PIN_9
#define RELAY_R_CTRL_GPIO_Port GPIOA
#define DC_FAULT_LED_Pin GPIO_PIN_11
#define DC_FAULT_LED_GPIO_Port GPIOA
#define WAIT_LED_Pin GPIO_PIN_12
#define WAIT_LED_GPIO_Port GPIOA
#define OVERHEAT_LED_Pin GPIO_PIN_4
#define OVERHEAT_LED_GPIO_Port GPIOB
#define TEMP1_FAIL_LED_Pin GPIO_PIN_8
#define TEMP1_FAIL_LED_GPIO_Port GPIOB

/* USER CODE BEGIN Private defines */

/* USER CODE END Private defines */

#ifdef __cplusplus
}
#endif

#endif /* __MAIN_H */
